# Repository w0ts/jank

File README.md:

# jank

**Ableton Link with no router.** jank protocol brings computers, MIDI gear and modular gear into a
**jank** session: the group mode of [Optimist](https://github.com/w0ts/optimist), the open firmware for the FM-1 synth
(**MODE JANK**, first called jam).

## No router

Link normally needs every player on the same network: a Wi-Fi router or access point that somebody sets up, joins and
keeps running. In jank there is none. The units send open Wi-Fi frames straight to each other on the group's channel,
with no association, no password and no host; the ones set to the same GROUP (1..9) hear each other and form one Link
session. Switch on, pick the group, play: on a stage, outdoors, wherever there is no network. How the frames look:
[docs/air.md](docs/air.md).

FM-1s running Optimist do this by themselves. **The jank device** speaks the same air format, so whatever is plugged
into it joins the group too.

## What joins through it

- **A computer, over the network.** On the device's USB port the computer sees a USB network adapter on the group, so
  any app with Ableton Link (Live, Bitwig…) joins the same session as the FM-1s.
- **A computer or a USB device, by MIDI clock.** The device is a USB-MIDI device for a computer, and a USB-MIDI host for
  gear with a USB port.
- **MIDI gear.** MIDI outputs send clock, start and stop locked to the session.
- **Modular gear.** Clock outputs, 5 V pulses.

It plays no sound: it follows the group's tempo and phase and sends them on. Link is Ableton's trademark; jank is not an
Ableton product.

## Two devices

- **The stick:** a bare Seeed XIAO ESP32-S3 (about US$7.50) in a computer or any USB host that speaks MIDI clock or Link (network driver). One button, one LED.
- **The jank box:** the same firmware on its own board, in a printed box.

The box has:
- 3 MIDI outs
- 1 MIDI in/out (TRS + DIN)
- 2 modular clock outs

## Build it

- [PCB](hardware/pcb/README.md)
- [Box](hardware/box/README.md)
- [Firmware](docs/firmware.md)

Details: [on the air](docs/air.md), [USB](docs/usb.md), [MIDI clock](docs/midi.md), [boards and pins](docs/boards.md).

## Licensing

The firmware (`firmware/`, `core/`, `tests/`, `scripts/`) is GPL-3.0-only, as it links Optimist's `link.c`
(`third_party/link`, copied from fm1-base, see its README). The control page and its test are MIT. The hardware
scripts carry GPL-3.0-only SPDX tags (`hardware/pcb/lib/stitch.py` CC0-1.0); the KiCad footprint of the XIAO is Seeed's,
CC BY-SA 4.0. See [LICENSE](LICENSE).

The pictures (`docs/img/`) are rendered from the box and board models by `docs/img/hero.scad`.

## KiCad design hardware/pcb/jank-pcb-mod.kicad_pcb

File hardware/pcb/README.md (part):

# jank board: schematic and layout for review

Part of the **[jank device](../../README.md)** · the other half: [the box](../box/README.md)

A carrier board for a **Seeed XIAO ESP32S3**: jank as one stick with a second USB-C for power, **a 0.91" OLED, an
encoder and two buttons (OK, BACK) on the lid side**, one RGB beat LED and **four MIDI outputs**. **v5 fits both
connectors on every output**: a right-angle 3.5 mm jack (XKB PJ-320D-B-SMT, surface mount) on the **top** and a DIN-5
(HOOYA DIN-504B-M10) on the **bottom**, **the jack beside the DIN** (v5c, 2026-11-09: between two DIN plates at a 23.0 mm
pitch, so nothing of the jack goes through the board under a DIN body) on the same nets (in parallel: **plug one at a
time**), and a **TRS type A / B slide switch** per output for the jack. **Both faces sit at the box wall** (the box
brings the board edge to 1.0 mm inside its outer face). **OUT1 doubles as a MIDI IN** under software control (an H11L1 behind a MOSFET
gate; its source cut by a second MOSFET). **Three outputs (OUT2, OUT3, OUT4) are on the front edge; OUT1 is on the back
edge** beside the two USB-Cs. **The top of the board is the lid side**: the XIAO, the screen, the encoder, the buttons,
the LED, the jacks and the A/B switches; the bottom carries only the DINs and the standing resistors (hand-soldered), and the
board stands about 20 mm above the box's floor on the DINs. Everything is hand-solderable: through-hole DINs,
switches, encoder, opto and swappable resistors, the jacks' four tabs, SOT-23 / SC-70 ICs, 0805 / 1206 passives, an LED
with lengthened pads. **The modular board (the one built): 87.0 x 79.5 mm, 2 layers.** (The plain 84 x 67 variant is
parked since v5c: with the 23 mm pitch its OUT4 resistor group lands on the encoder; `make_fab.sh` builds `-mod` only.)

> **Stage: schematic and layout, v5 (2026-11-08).** Nothing is ordered, built or measured. Every value marked
> *unverified* below was not checked against the part or a datasheet in this session.

The drawing: [`jank-pcb-mod-schematic.pdf`](jank-pcb-mod-schematic.pdf). The board: [`render-top-mod.png`](render-top-mod.png),
[`render-bottom-mod.png`](render-bottom-mod.png).

## v5c (2026-11-09): the jack beside the DIN, both faces at the wall

The user, on seeing v5's stacked connectors: *"the jacks are not reachable from the outside of the box ... put the midi
jack between the DIN plugs on the pcb, making sure the pins don't collide (DIN on one side, jack on the other)"*, and
*"DIN AND jack should be at the wall"*.

- **Each output's 3.5 mm jack moved 11.5 mm along the edge**, into the 2.1 mm gap between two DIN plates (the pitch
  went from 21.1 to **23.0 mm**; the board from 84 to **87 mm** wide so OUT4's resistor group clears the right
  channels' drivers, which moved 3 mm right with the wall jacks and the holes H1 / H2). OUT4's jack is right of the
  last DIN; **OUT1's jack is left of its DIN at the back-left corner** (DIN axis x 17.5, jack x 6.0).
- **The jack is now the surface-mount twin, XKB PJ-320D-B-SMT (C2884940)**: same body, bushing and pegs, four 1.5 x 2.5
  tabs on the top instead of legs through the board (the legs would have come out under the neighbouring DIN bodies).
  Its two 1.3 mm pegs sit in the gap, 0.4 mm from each DIN body. The side-wall jacks J11..J14 stay the through-hole
  PJ-320A (nothing is under them).
- **The DIN plate is 1.0 mm behind the board edge, the jack body front 0.5 mm past it.** The box puts the board edge
  1.0 mm inside its outer face on the connector edges: **the DIN faces are flush with the outside, the jack bodies 0.5 mm
  inside it with the bushings 1.5 mm proud**. The 1.0 mm also keeps the jack's rear tab pads 0.3 mm from the next DIN's
  pin 1 / 3 pads (the rows interleave: DIN pins at 13.3 and 15.8 in, jack tabs at 2.5 .. 11.0 in).
- **OUT1's A/B switch SW2 is the surface-mount XKB SS-3235S-L2 (C500056)**, over the DIN body at (17.5, 8.1): a
  through-hole switch's pins would hit the DIN under the board, and the strip east of the DIN carries the XIAO's MIDI IN
  lines (IN_EN, MIDI_RX, TX1). Same pinout (1-2-3 / 4-5-6, 2 and 5 the commons), knob 3.0 mm, travel 1.5 mm along x.
  SW3..SW5 stay the through-hole MSS22D18 (their pins land behind the DIN bodies).
- Routes: each jack's tip and ring reach their tabs through a via next to the pad (the switches' routes run on the
  bottom); OUT1's TIP throw crosses under the switch through two vias.
- Prices of the two new parts not read (LCSC refused the page on 2026-11-09): **0.00 in the BOM**, fill in before
  trusting the total.
- **The MIDI resistors are 1206s placed by JLC (later on 2026-11-09, the user: "the upright resistors are just post
  fixes"):** R3k 10 ohm (C17903), the source two 68 ohm in parallel, R4k + R8k (C17976; 34 ohm, 0.5 W together, for a
  mono plug on a TRS output: 0.33 W), R9 330 ohm for the LED (C17930). R8k sits where the 33 ohm group's bypass jumper
  JP2k was (gone). The axial pads (R1k, R2k, R8) stay, empty ("DNP fix"): a bench fix solders an axial part there with
  the 1206s removed. The 10 ohm group keeps its bypass jumper JP1k.
- **The screen is the 0.96" 128 x 64 OLED** (HS96L03W2C03, C5248080; the user, 2026-11-09): 27.3 x 27.8 on its header
  at (34.58, 24.0); the PCF8574 moved right of it; SDA / SCL swapped on the XIAO (SDA D8 = GPIO7, SCL D9 = GPIO8); the
  expander's right channels on P2 / P3, P4..P7 on test pads.

## v5 in short (what changed from round 7 / 2026-11-08)

- **Both connectors fitted, two rows on the front wall:** the jacks above the board, the DIN faces below it (OUT1 the
  same on the back wall). The DIN's footprint is mirrored onto the bottom; its plate sits **1.0 mm behind the edge**
  (the jacks' fronts stay on the edge) so its pin 2 clears the jack's back (below, "Both connectors").
- **The lid side is the top:** the XIAO, the OLED, OK, BACK, the encoder, one LED, the jacks, the A/B switches. Seen
  from the front with the lid up the outputs read **2, 3, 4 left to right** (OUT2 is now at x 10.45).
- **Pins:** OUT2, OUT3 and OUT4 share **one TX pad** (GPIO2); OUT1 keeps its own (GPIO1, Hi-Z in IN mode). That frees
  GPIO7 / GPIO8 for **I2C** (the OLED); IN_EN and MIDI_RX moved to GPIO5 / GPIO6, the LED to GPIO4.
- **The buttons are OK (menu / select) and BACK** (were MODE and PLAY/STOP): the same parts and ladder values.
- **One LED**, top-emitting (SK6812MINI-HS); the second LED and the reverse-mount cut-outs are gone.
- **4 M2 holes** (two right corners, two on the left edge between OUT1 and OUT2).
- **The standing resistors hang under the board** (beside the DINs); their jumpers and parallel pads stay on top.
- **BOM:** one board, 4 jacks + 4 DINs + 4 A/B switches, the OLED, one LED: **USD 17.49** at unit prices, **USD 30.84**
  with each shop's minimum order (`BOM.md`).

## Files

| File | What |
|---|---|
| `make_schematic.py` | The schematic, the project (with the board's rules), the XIAO and switch symbols, the intended nets and `BOM.md`, from one parts table |
| `make_footprints.py` | The v5 output footprint `MIDI_OUT_PJ-320A_top_DIN-504B-M10_bottom`, the LED `LED_SK6812MINI-HS_3.7x3.5mm_HandSolder`, the OLED header `OLED_0.91in_128x32_I2C_HS91L02W2C01`, the A/B slide switch, the XIAO on headers, and the older output footprints (`lib/jank.pretty/`) |
| `make_board.py` | `jank-pcb.kicad_pcb`: placement, routes, pours, stitching vias, silk (KiCad's Python). Its `square` layout (an older 67 x 58 board) is unused and not built |
| `make_mockup.py` | `mockup.stl` (its `mockup.scad` is rebuilt, not kept): the board and its parts as one solid, both sides, checked by `../check_stl.py` |
| `make_assembly.py` | `fab/bom.csv` and `fab/cpl.csv`: JLCPCB's assembly files (README "Assembly") |
| `check_nets.py` | The netlist against the intent and the design rules (the A/B switches, the shared TX pad, the MIDI IN, the controls, the OLED), and the board's pads against the schematic |
| `make_fab.sh` | All of it in order, for both projects (v5 and the modular variant, `MODULAR=1`): schematic, ERC, PDF, the board, DRC, nets, Gerbers + drill, the assembly files, renders, mockup |
| `jank-pcb.kicad_sch`, `jank-pcb.kicad_pcb`, `jank-pcb.kicad_pro`, `sym-lib-table`, `fp-lib-table` | The KiCad 10 project (generated) |
| `lib/jank.kicad_sym` | The XIAO ESP32S3 and DPDT slide switch symbols (drawn by `make_schematic.py`) |
| `lib/jank.pretty/XIAO-ESP32-S3-DIP.kicad_mod` | Seeed's footprint, unchanged (source below) |
| `lib/jank.pretty/XIAO-ESP32-S3-DIP_Headers.kicad_mod` | The same with its courtyard on the two pin rows only (written by `make_footprints.py`): on headers, low parts fit under the module |
| `lib/stitch.py` | The ground stitching vias, from optimist's SD board (after m-card, CC0-1.0) |
| `jank-pcb-schematic.pdf`, `render-top.png`, `render-bottom.png` | The schematic (A2) and the board's renders |
| `fab/jank-pcb-gerbers.zip` | **For JLCPCB** (bare board): the Gerbers and the PTH / NPTH drill files, origin at the lower left (the `fab/gerbers/` folder and the reports are rebuilt by `make_fab.sh`, not kept) |
| `fab/bom.csv`, `fab/cpl.csv` | **For JLCPCB's assembly**: the SMD parts it places and where (generated by `make_assembly.py`); `fab/full/` the same with the through-hole parts, for later |
| `BOM.md` | Parts, one price each, shop and date (generated) |
| `jank-pcb-mod.*`, `BOM-mod.md`, `fab/mod/`, `render-*-mod.png`, `mockup-mod.stl`, `jank-pcb-mod-schematic.pdf` | The modular variant (README "Modular variant") |

```
sh hardware/pcb/make_fab.sh        # needs KiCad 10 (kicad-cli and its Python), python3, OpenSCAD
```

**Last run (2026-11-08, v5):**
- ERC: **0 errors, 0 warnings**.
- DRC: **0 errors, 0 unconnected, 28 warnings**: 21 "silkscreen over copper" (Seeed's XIAO outline over its own pads,
  the A/B switches' outlines and their "OUTk A|B" labels over tracks, one LED outline line over its data track) and 7
  "silkscreen clipped by the board edge" (the XIAO's USB-C lip drawn past the back edge, where the socket really
  overhangs).
- `check_nets.py`: 243 schematic pins, 45 nets, 0 problems; **278 board pads against the schematic, 0 differences**.
- Mockup: `mockup.stl` one body, **0 open edges**, 0 non-manifold, 0 misoriented.

**XIAO footprint source:** `XIAO-ESP32-S3-DIP.kicad_mod` from Seeed's
[OPL_Kicad_Library](https://github.com/Seeed-Studio/OPL_Kicad_Library), folder "Seeed Studio XIAO Series Library",
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
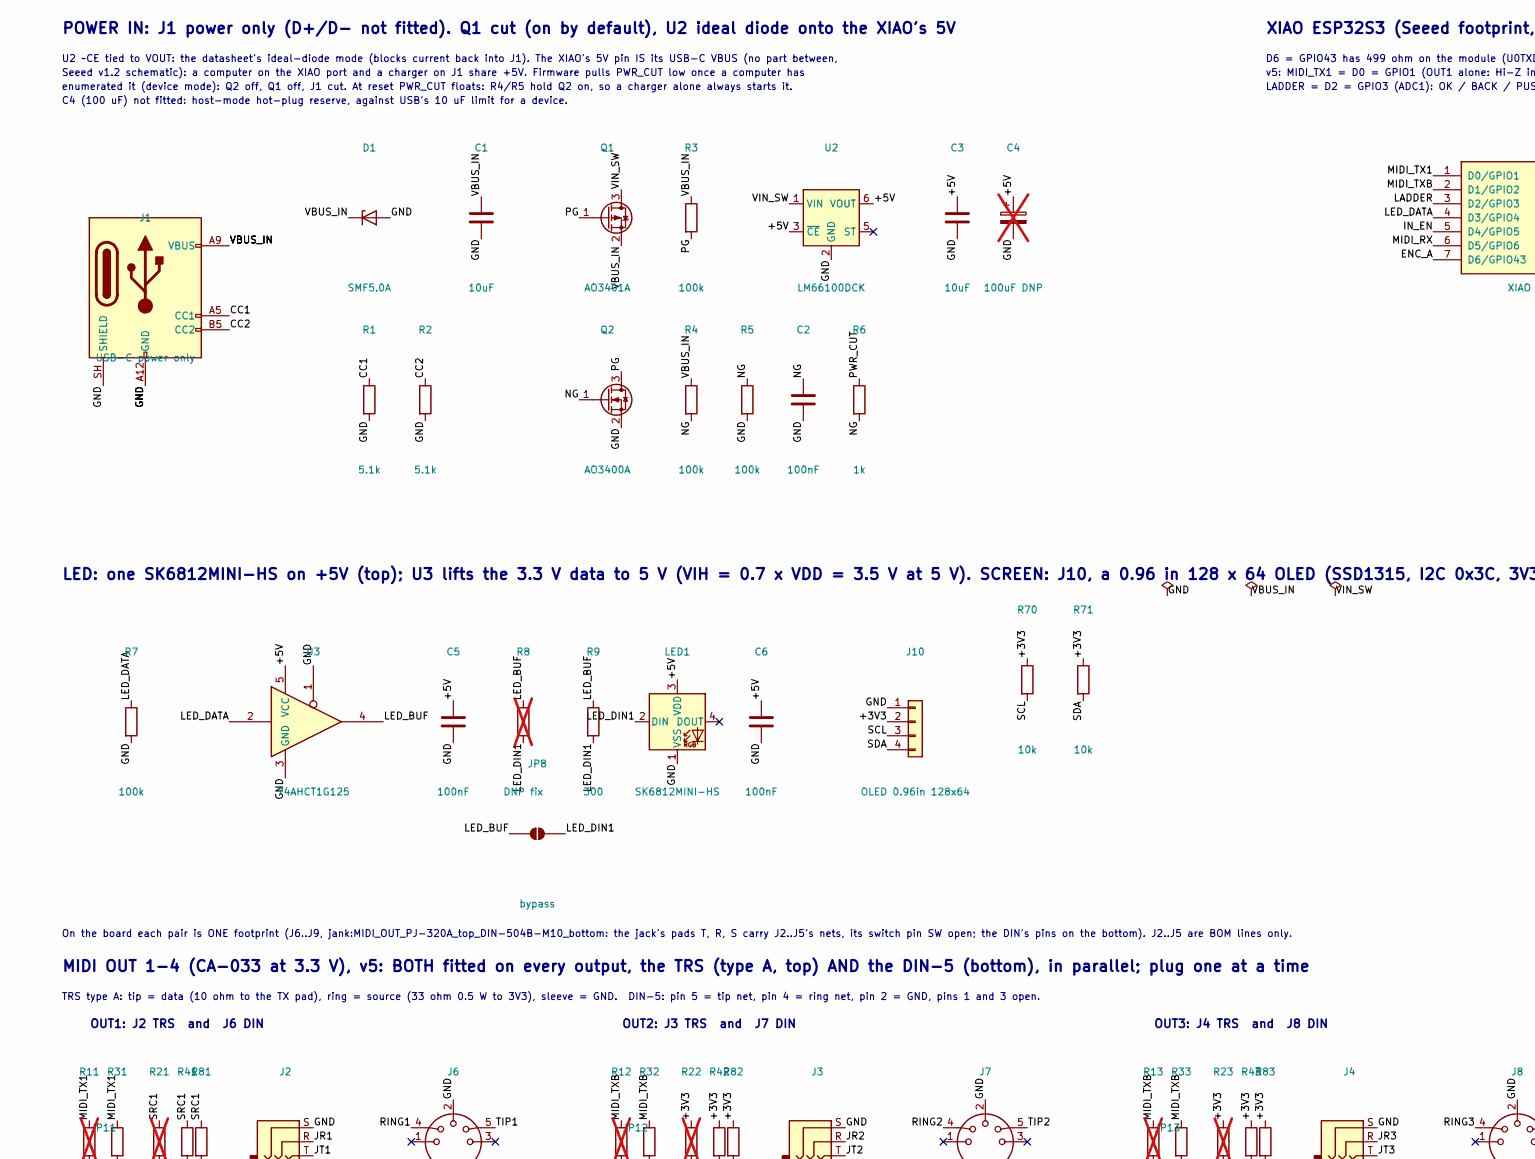
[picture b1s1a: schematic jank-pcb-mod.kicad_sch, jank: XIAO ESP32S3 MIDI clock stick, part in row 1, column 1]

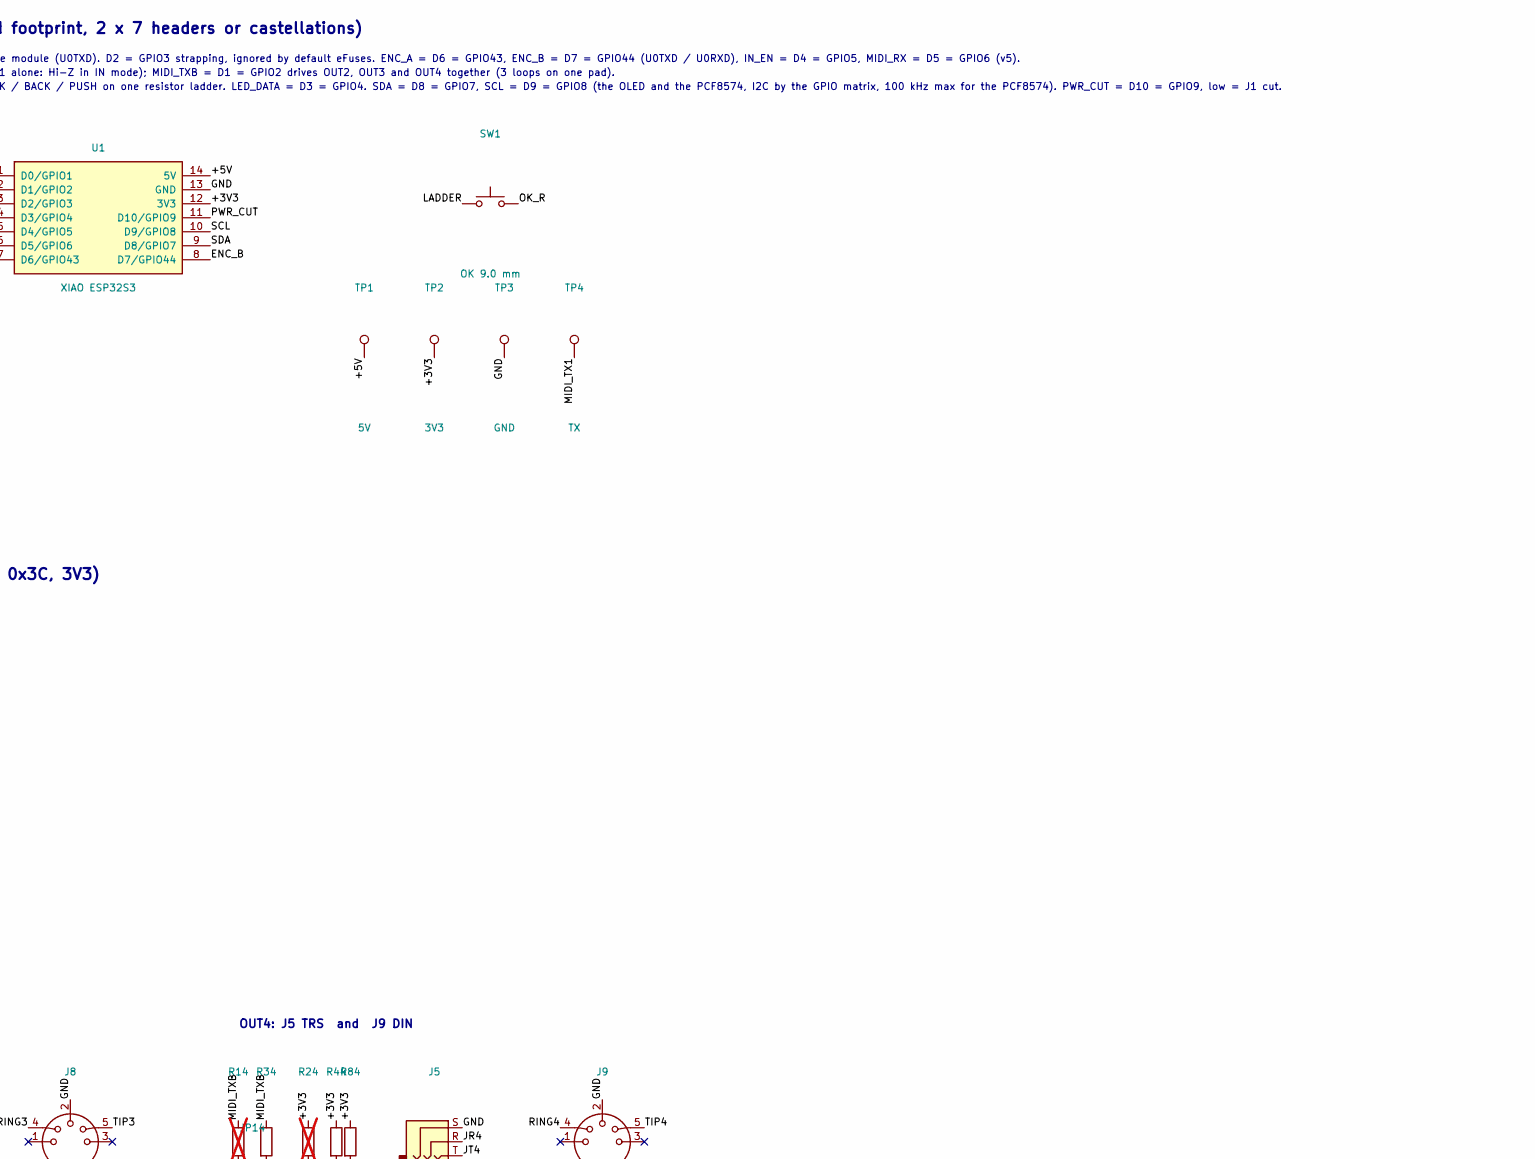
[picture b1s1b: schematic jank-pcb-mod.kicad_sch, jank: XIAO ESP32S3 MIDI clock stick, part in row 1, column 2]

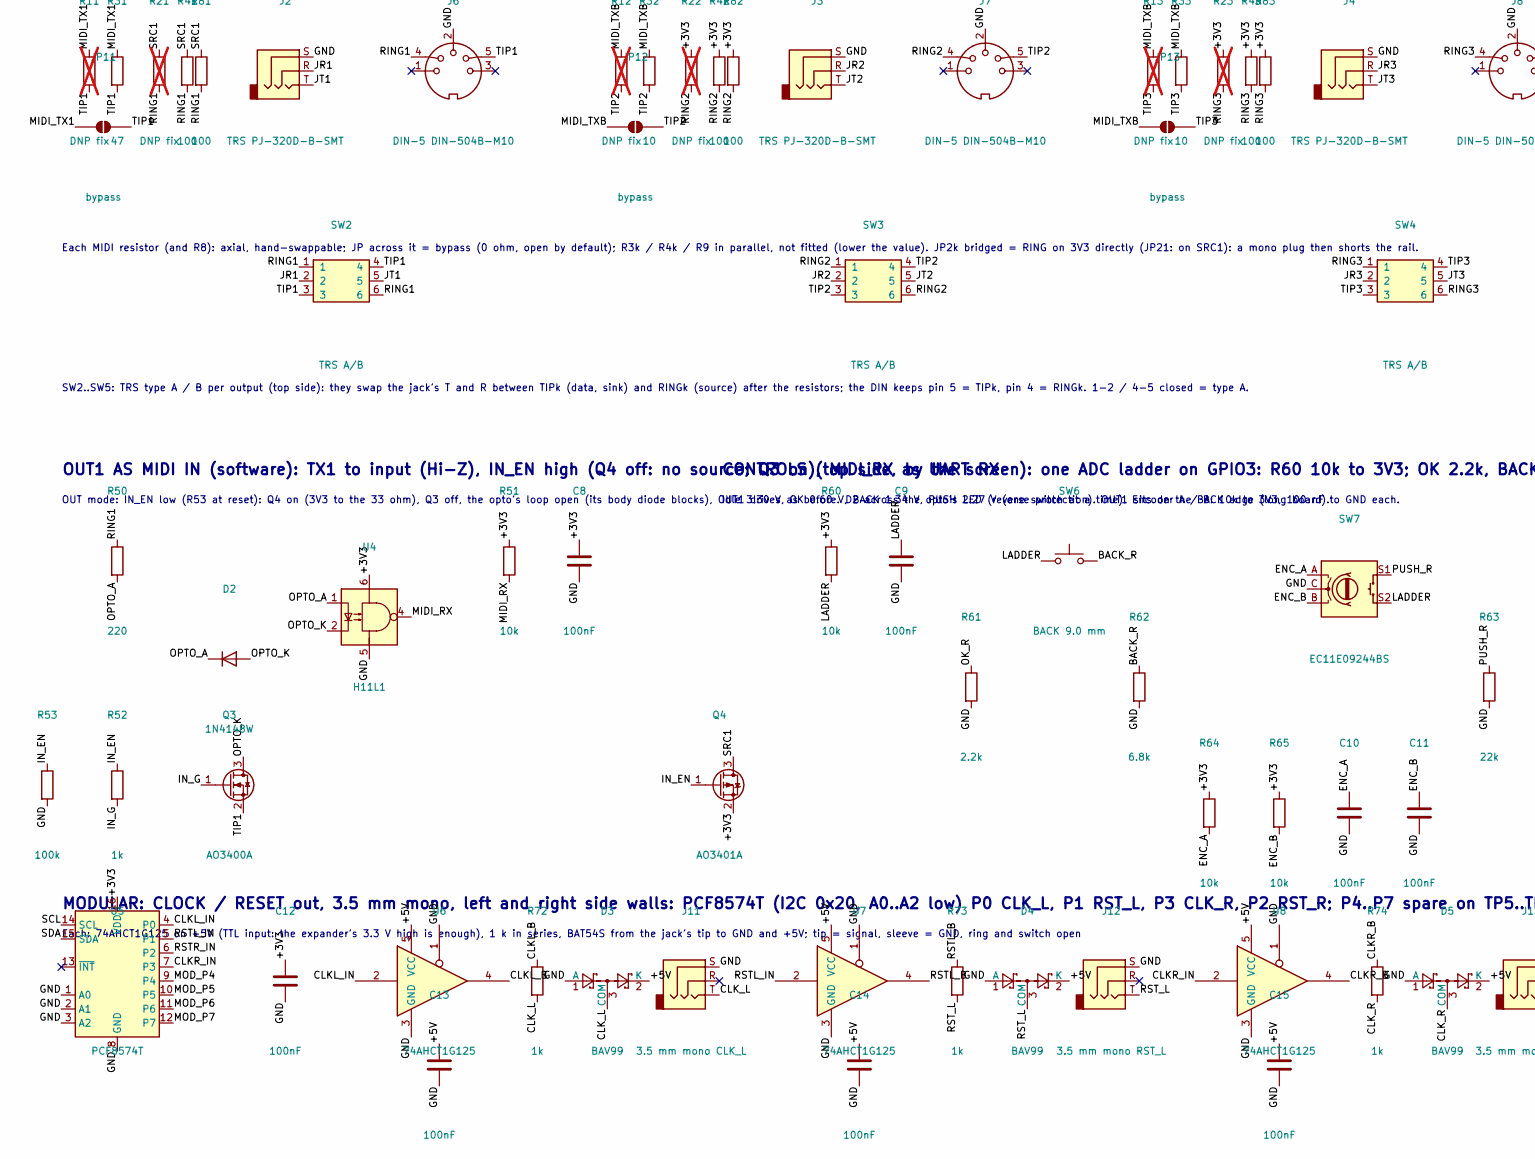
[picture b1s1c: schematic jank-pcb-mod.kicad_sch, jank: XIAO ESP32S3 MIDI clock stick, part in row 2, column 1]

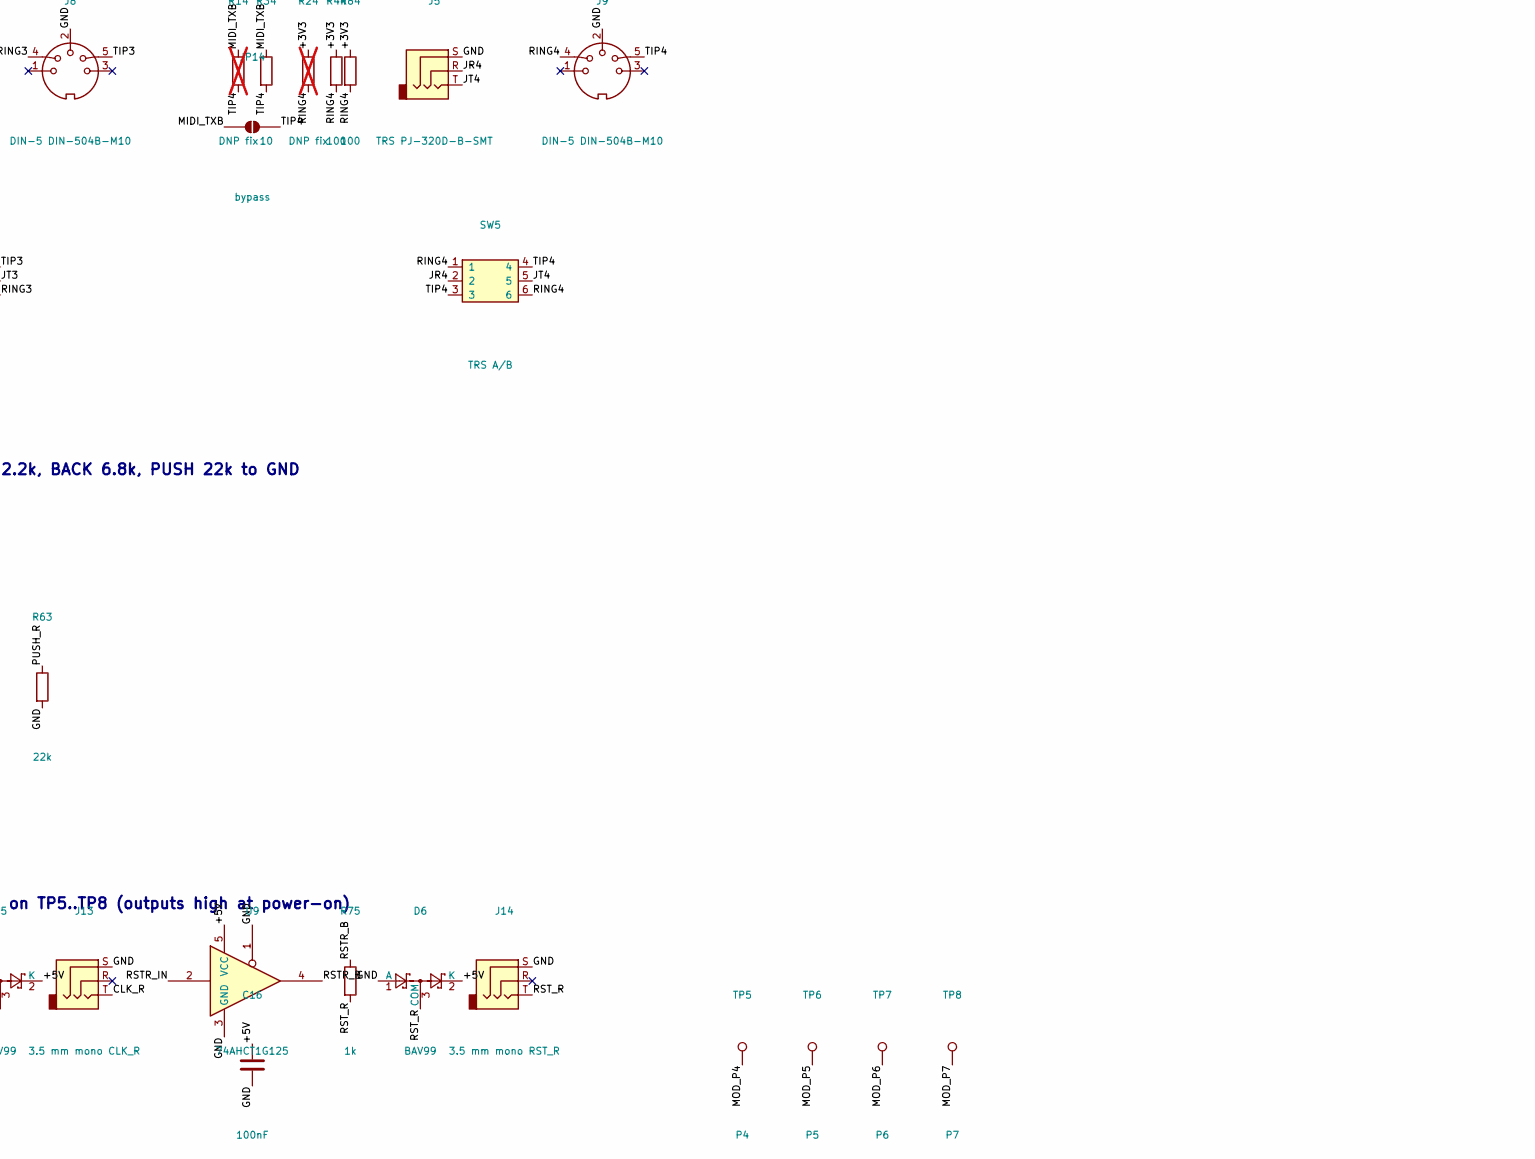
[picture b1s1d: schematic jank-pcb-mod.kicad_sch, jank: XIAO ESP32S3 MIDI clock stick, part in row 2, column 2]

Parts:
C1, C3: 10uF; C_0805_2012Metric_Pad1.18x1.45mm_HandSolder; MPN Samsung CL21A106KAYNNNE
C2, C5, C6, C8, C9, C10, C11, C12, C13, C14, C15, C16: 100nF; C_0805_2012Metric_Pad1.18x1.45mm_HandSolder; MPN YAGEO CC0805KRX7R9BB104
C4: 100uF DNP; CP_Elec_5x5.4; MPN ROQANG RVT1C101M0505; not fitted
D1: SMF5.0A; D_SOD-123F; MPN MDD SMF5.0A
D2: 1N4148W; D_SOD-123; MPN Semtech 1N4148W
D3, D4, D5, D6: BAV99; SOT-23; MPN BAV99
J1: USB-C power only; USB_C_SHOUHAN_TYPE-C-6P; MPN SHOU HAN TYPE-C 6P
J2, J3, J4, J5: TRS PJ-320D-B-SMT; MPN XKB PJ-320D-B-SMT
J6, J7, J8, J9: DIN-5 DIN-504B-M10; MIDI_OUT_PJ-320A_top_DIN-504B-M10_bottom; MPN HOOYA DIN-504B-M10
J10: OLED 0.96in 128x64; OLED_0.96in_128x64_I2C_HS96L03W2C03; MPN HS HS96L03W2C03
J11: 3.5 mm mono CLK_L; Jack_3.5mm_XKB_PJ-320A_Horizontal; MPN XKB PJ-320A
J12: 3.5 mm mono RST_L; Jack_3.5mm_XKB_PJ-320A_Horizontal; MPN XKB PJ-320A
J13: 3.5 mm mono CLK_R; Jack_3.5mm_XKB_PJ-320A_Horizontal; MPN XKB PJ-320A
J14: 3.5 mm mono RST_R; Jack_3.5mm_XKB_PJ-320A_Horizontal; MPN XKB PJ-320A
JP8, JP11, JP12, JP13, JP14: bypass; SolderJumper-2_P1.3mm_Open_RoundedPad1.0x1.5mm
LED1: SK6812MINI-HS; LED_SK6812MINI-HS_3.7x3.5mm_HandSolder; MPN OPSCO SK6812MINI-HS
Q1, Q4: AO3401A; SOT-23; MPN AOS AO3401A
Q2, Q3: AO3400A; SOT-23; MPN AOS AO3400A
R1, R2: 5.1k; R_0805_2012Metric_Pad1.20x1.40mm_HandSolder; MPN UNI-ROYAL 0805W8F5101T5E
R3, R4, R5, R7, R53: 100k; R_0805_2012Metric_Pad1.20x1.40mm_HandSolder; MPN UNI-ROYAL 0805W8F1003T5E
R6, R52, R72, R73, R74, R75: 1k; R_0805_2012Metric_Pad1.20x1.40mm_HandSolder; MPN UNI-ROYAL 0805W8F1001T5E
R8, R11, R12, R13, R14: DNP fix; R_Axial_DIN0207_L6.3mm_D2.5mm_P2.54mm_Vertical; not fitted
R9: 300; R_1206_3216Metric_Pad1.30x1.75mm_HandSolder; MPN UNI-ROYAL 1206W4F3000T5E
R21, R22, R23, R24: DNP fix; R_Axial_DIN0309_L9.0mm_D3.2mm_P2.54mm_Vertical; not fitted
R31: 47; R_1206_3216Metric_Pad1.30x1.75mm_HandSolder; MPN UNI-ROYAL 1206W4F470JT5E
R32, R33, R34: 10; R_1206_3216Metric_Pad1.30x1.75mm_HandSolder; MPN UNI-ROYAL 1206W4F100JT5E
R41, R42, R43, R44, R81, R82, R83, R84: 100; R_1206_3216Metric_Pad1.30x1.75mm_HandSolder; MPN UNI-ROYAL 1206W4F1000T5E
R50: 220; R_0805_2012Metric_Pad1.20x1.40mm_HandSolder; MPN UNI-ROYAL 0805W8F2200T5E
R51, R60, R64, R65, R70, R71: 10k; R_0805_2012Metric_Pad1.20x1.40mm_HandSolder; MPN UNI-ROYAL 0805W8F1002T5E
R61: 2.2k; R_0805_2012Metric_Pad1.20x1.40mm_HandSolder; MPN UNI-ROYAL 0805W8F2201T5E
R62: 6.8k; R_0805_2012Metric_Pad1.20x1.40mm_HandSolder; MPN UNI-ROYAL 0805W8F6801T5E
R63: 22k; R_0805_2012Metric_Pad1.20x1.40mm_HandSolder; MPN UNI-ROYAL 0805W8F2202T5E
SW1: OK 9.0 mm; SW_PUSH_6mm; MPN HRO K2-1102DP-K4SW-04
SW2: TRS A/B; SW_Slide_DPDT_SS3235S_SMD; MPN XKB SS-3235S-L2
SW3, SW4, SW5: TRS A/B; SW_Slide_DPDT_MSS22D18; MPN SHOU HAN MSS22D18G2
SW6: BACK 9.0 mm; SW_PUSH_6mm; MPN HRO K2-1102DP-K4SW-04
SW7: EC11E09244BS; RotaryEncoder_Alps_EC11E-Switch_Vertical_H20mm; MPN ALPS EC11E09244BS
TP1: 5V; TestPoint_Pad_D1.5mm
TP2: 3V3; TestPoint_Pad_D1.5mm
TP3: GND; TestPoint_Pad_D1.5mm
TP4: TX; TestPoint_Pad_D1.5mm
TP5: P4; TestPoint_Pad_D1.0mm
TP6: P5; TestPoint_Pad_D1.0mm
TP7: P6; TestPoint_Pad_D1.0mm
TP8: P7; TestPoint_Pad_D1.0mm
U1: XIAO ESP32S3; XIAO-ESP32-S3-DIP; MPN 113991114
U2: LM66100DCK; SOT-363_SC-70-6; MPN TI LM66100DCKR
U3, U6, U7, U8, U9: 74AHCT1G125; SOT-23-5_HandSoldering; MPN TI SN74AHCT1G125DBVR
U4: H11L1; DIP-6_W7.62mm; MPN EVERLIGHT H11L1
U5: PCF8574T; SOIC-16W_7.5x10.3mm_P1.27mm; MPN NXP PCF8574T/3

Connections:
+3V3: C8.1, C12.1, J10.2, Q4.2 (S), R22.1, R23.1, R24.1, R42.1, R43.1, R44.1, R51.1, R60.1, R64.1, R65.1, R70.1, R71.1, R82.1, R83.1, R84.1, TP2.1, U1.12 (3V3), U4.6, U5.16 (VDD)
+5V: C3.1, C4.1, C5.1, C6.1, C13.1, C14.1, C15.1, C16.1, D3.2 (K), D4.2 (K), D5.2 (K), D6.2 (K), LED1.3 (VDD), TP1.1, U1.14 (5V), U2.3 (~CE), U2.6 (VOUT), U3.5 (VCC), U6.5 (VCC), U7.5 (VCC), U8.5 (VCC), U9.5 (VCC)
BACK_R: R62.1, SW6.2
CC1: J1.A5 (CC1), R1.1
CC2: J1.B5 (CC2), R2.1
CLKL_B: R72.1, U6.4
CLKL_IN: U5.4 (P0), U6.2
CLKR_B: R74.1, U8.4
CLKR_IN: U5.7 (P3), U8.2
CLK_L: D3.3 (COM), J11.T, R72.2
CLK_R: D5.3 (COM), J13.T, R74.2
ENC_A: C10.1, R64.2, SW7.A, U1.7 (D6/GPIO43)
ENC_B: C11.1, R65.2, SW7.B, U1.8 (D7/GPIO44)
GND: C1.2, C2.2, C3.2, C4.2, C5.2, C6.2, C8.2, C9.2, C10.2, C11.2, C12.2, C13.2, C14.2, C15.2, C16.2, D1.2 (A), D3.1 (A), D4.1 (A), D5.1 (A), D6.1 (A), J1.A12 (GND), J1.B12 (GND), J1.SH (SHIELD), J2.S, J3.S, J4.S, J5.S, J6.2, J6.E, J6.S, J7.2, J7.E, J7.S, J8.2, J8.E, J8.S, J9.2, J9.E, J9.S, J10.1, J11.S, J12.S, J13.S, J14.S, LED1.1 (VSS), Q2.2 (S), R1.2, R2.2, R5.2, R7.2, R53.2, R61.2, R62.2, R63.2, SW7.C, TP3.1, U1.13 (GND), U2.2 (GND), U3.1, U3.3 (GND), U4.5, U5.1 (A0), U5.2 (A1), U5.3 (A2), U5.8 (GND), U6.1, U6.3 (GND), U7.1, U7.3 (GND), U8.1, U8.3 (GND), U9.1, U9.3 (GND)
IN_EN: Q4.1 (G), R52.1, R53.1, U1.5 (D4/GPIO5)
IN_G: Q3.1 (G), R52.2
JR1: J2.R, J6.R, SW2.2
JR2: J3.R, J7.R, SW3.2
JR3: J4.R, J8.R, SW4.2
JR4: J5.R, J9.R, SW5.2
JT1: J2.T, J6.T, SW2.5
JT2: J3.T, J7.T, SW3.5
JT3: J4.T, J8.T, SW4.5
JT4: J5.T, J9.T, SW5.5
LADDER: C9.1, R60.2, SW1.1, SW6.1, SW7.S2, U1.3 (D2/GPIO3)
LED_BUF: JP8.1 (A), R8.1, R9.1, U3.4
LED_DATA: R7.1, U1.4 (D3/GPIO4), U3.2
LED_DIN1: JP8.2 (B), LED1.2 (DIN), R8.2, R9.2
MIDI_RX: R51.2, U1.6 (D5/GPIO6), U4.4
MIDI_TX1: JP11.1 (A), R11.1, R31.1, TP4.1, U1.1 (D0/GPIO1)
MIDI_TXB: JP12.1 (A), JP13.1 (A), JP14.1 (A), R12.1, R13.1, R14.1, R32.1, R33.1, R34.1, U1.2 (D1/GPIO2)
MOD_P4: TP5.1, U5.9 (P4)
MOD_P5: TP6.1, U5.10 (P5)
MOD_P6: TP7.1, U5.11 (P6)
MOD_P7: TP8.1, U5.12 (P7)
NG: C2.1, Q2.1 (G), R4.2, R5.1, R6.2
OK_R: R61.1, SW1.2
OPTO_A: D2.1 (K), R50.2, U4.1
OPTO_K: D2.2 (A), Q3.3 (D), U4.2
PG: Q1.1 (G), Q2.3 (D), R3.2
PUSH_R: R63.1, SW7.S1
PWR_CUT: R6.1, U1.11 (D10/GPIO9)
RING1: J6.4, R21.2, R41.2, R50.1, R81.2, SW2.1, SW2.6
RING2: J7.4, R22.2, R42.2, R82.2, SW3.1, SW3.6
RING3: J8.4, R23.2, R43.2, R83.2, SW4.1, SW4.6
RING4: J9.4, R24.2, R44.2, R84.2, SW5.1, SW5.6
RSTL_B: R73.1, U7.4
RSTL_IN: U5.5 (P1), U7.2
RSTR_B: R75.1, U9.4
RSTR_IN: U5.6 (P2), U9.2
RST_L: D4.3 (COM), J12.T, R73.2
RST_R: D6.3 (COM), J14.T, R75.2
SCL: J10.3, R70.2, U1.10 (D9/GPIO8), U5.14 (SCL)
SDA: J10.4, R71.2, U1.9 (D8/GPIO7), U5.15 (SDA)
SRC1: Q4.3 (D), R21.1, R41.1, R81.1
TIP1: J6.5, JP11.2 (B), Q3.2 (S), R11.2, R31.2, SW2.3, SW2.4
TIP2: J7.5, JP12.2 (B), R12.2, R32.2, SW3.3, SW3.4
TIP3: J8.5, JP13.2 (B), R13.2, R33.2, SW4.3, SW4.4
TIP4: J9.5, JP14.2 (B), R14.2, R34.2, SW5.3, SW5.4
VBUS_IN: C1.1, D1.1 (K), J1.A9 (VBUS), J1.B9 (VBUS), Q1.2 (S), R3.1, R4.1
VIN_SW: Q1.3 (D), U2.1 (VIN)

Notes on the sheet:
POWER IN: J1 power only (D+/D- not fitted). Q1 cut (on by default), U2 ideal diode onto the XIAO's 5V
U2 ~CE tied to VOUT: the datasheet's ideal-diode mode (blocks current back into J1). The XIAO's 5V pin IS its USB-C VBUS (no part between,
Seeed v1.2 schematic): a computer on the XIAO port and a charger on J1 share +5V. Firmware pulls PWR_CUT low once a computer has
enumerated it (device mode): Q2 off, Q1 off, J1 cut. At reset PWR_CUT floats: R4/R5 hold Q2 on, so a charger alone always starts it.
C4 (100 uF) not fitted: host-mode hot-plug reserve, against USB's 10 uF limit for a device.
XIAO ESP32S3 (Seeed footprint, 2 x 7 headers or castellations)
D6 = GPIO43 has 499 ohm on the module (U0TXD). D2 = GPIO3 strapping, ignored by default eFuses. ENC_A = D6 = GPIO43, ENC_B = D7 = GPIO44 (U0TXD / U0RXD), IN_EN = D4 = GPIO5, MIDI_RX = D5 = GPIO6 (v5).
v5: MIDI_TX1 = D0 = GPIO1 (OUT1 alone: Hi-Z in IN mode); MIDI_TXB = D1 = GPIO2 drives OUT2, OUT3 and OUT4 together (3 loops on one pad).
LADDER = D2 = GPIO3 (ADC1): OK / BACK / PUSH on one resistor ladder. LED_DATA = D3 = GPIO4. SDA = D8 = GPIO7, SCL = D9 = GPIO8 (the OLED and the PCF8574, I2C by the GPIO matrix, 100 kHz max for the PCF8574). PWR_CUT = D10 = GPIO9, low = J1 cut.
LED: one SK6812MINI-HS on +5V (top); U3 lifts the 3.3 V data to 5 V (VIH = 0.7 x VDD = 3.5 V at 5 V). SCREEN: J10, a 0.96 in 128 x 64 OLED (SSD1315, I2C 0x3C, 3V3)
MIDI OUT 1-4 (CA-033 at 3.3 V), v5: BOTH fitted on every output, the TRS (type A, top) AND the DIN-5 (bottom), in parallel; plug one at a time
TRS type A: tip = data (10 ohm to the TX pad), ring = source (33 ohm 0.5 W to 3V3), sleeve = GND. DIN-5: pin 5 = tip net, pin 4 = ring net, pin 2 = GND, pins 1 and 3 open.
OUT1: J2 TRS and J6 DIN
OUT2: J3 TRS and J7 DIN
OUT3: J4 TRS and J8 DIN
OUT4: J5 TRS and J9 DIN
SW2..SW5: TRS type A / B per output (top side): they swap the jack's T and R between TIPk (data, sink) and RINGk (source) after the resistors; the DIN keeps pin 5 = TIPk, pin 4 = RINGk. 1-2 / 4-5 closed = type A.
OUT1 AS MIDI IN (software): TX1 to input (Hi-Z), IN_EN high (Q4 off: no source; Q3 on), MIDI_RX as UART RX
OUT mode: IN_EN low (R53 at reset): Q4 on (3V3 to the 33 ohm), Q3 off, the opto's loop open (its body diode blocks), OUT1 drives as before. D2 across the opto's LED (reverse protection). OUT1 sits on the BACK edge (long board).
CONTROLS (top side, by the screen): one ADC ladder on GPIO3: R60 10k to 3V3; OK 2.2k, BACK 6.8k, PUSH 22k to GND
Idle 3.30 V, OK 0.60 V, BACK 1.34 V, PUSH 2.27 V (one switch at a time). Encoder A / B: 10k to 3V3, 100 nF to GND each.
Each MIDI resistor (and R8): axial, hand-swappable; JP across it = bypass (0 ohm, open by default); R3k / R4k / R9 in parallel, not fitted (lower the value). JP2k bridged = RING on 3V3 directly (JP21: on SRC1): a mono plug then shorts the rail.
On the board each pair is ONE footprint (J6..J9, jank:MIDI_OUT_PJ-320A_top_DIN-504B-M10_bottom: the jack's pads T, R, S carry J2..J5's nets, its switch pin SW open; the DIN's pins on the bottom). J2..J5 are BOM lines only.
MODULAR: CLOCK / RESET out, 3.5 mm mono, left and right side walls: PCF8574T (I2C 0x20, A0..A2 low) P0 CLK_L, P1 RST_L, P3 CLK_R, P2 RST_R; P4..P7 spare on TP5..TP8 (outputs high at power-on)
Each: 74AHCT1G125 on +5V (TTL input: the expander's 3.3 V high is enough), 1 k in series, BAT54S from the jack's tip to GND and +5V; tip = signal, sleeve = GND, ring and switch open

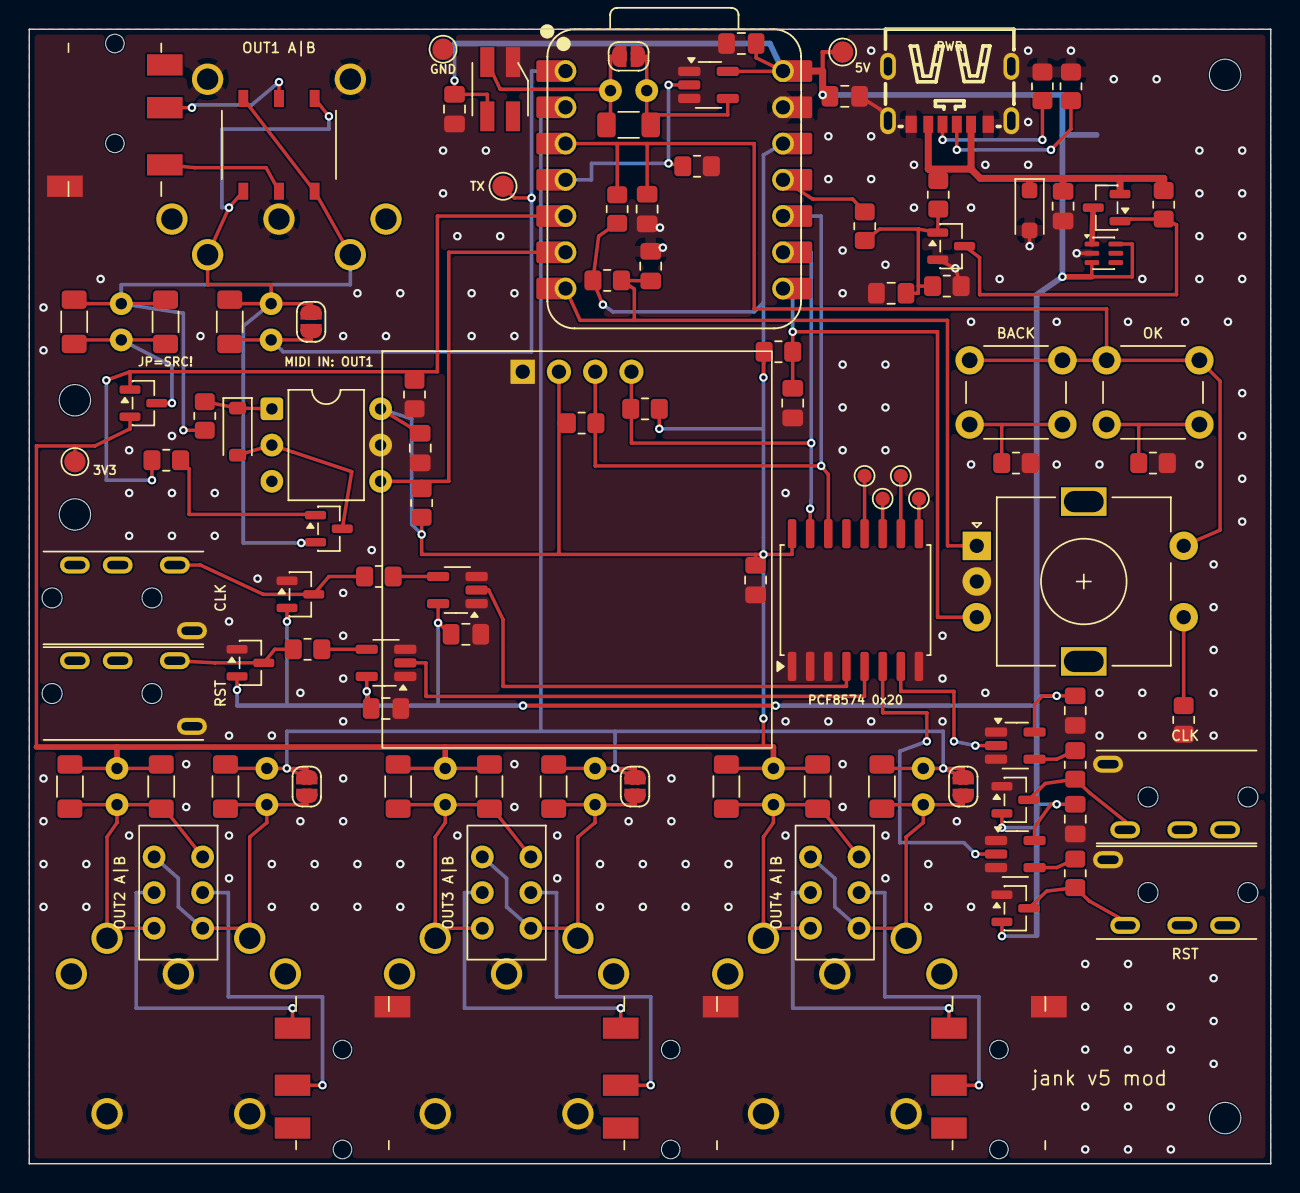
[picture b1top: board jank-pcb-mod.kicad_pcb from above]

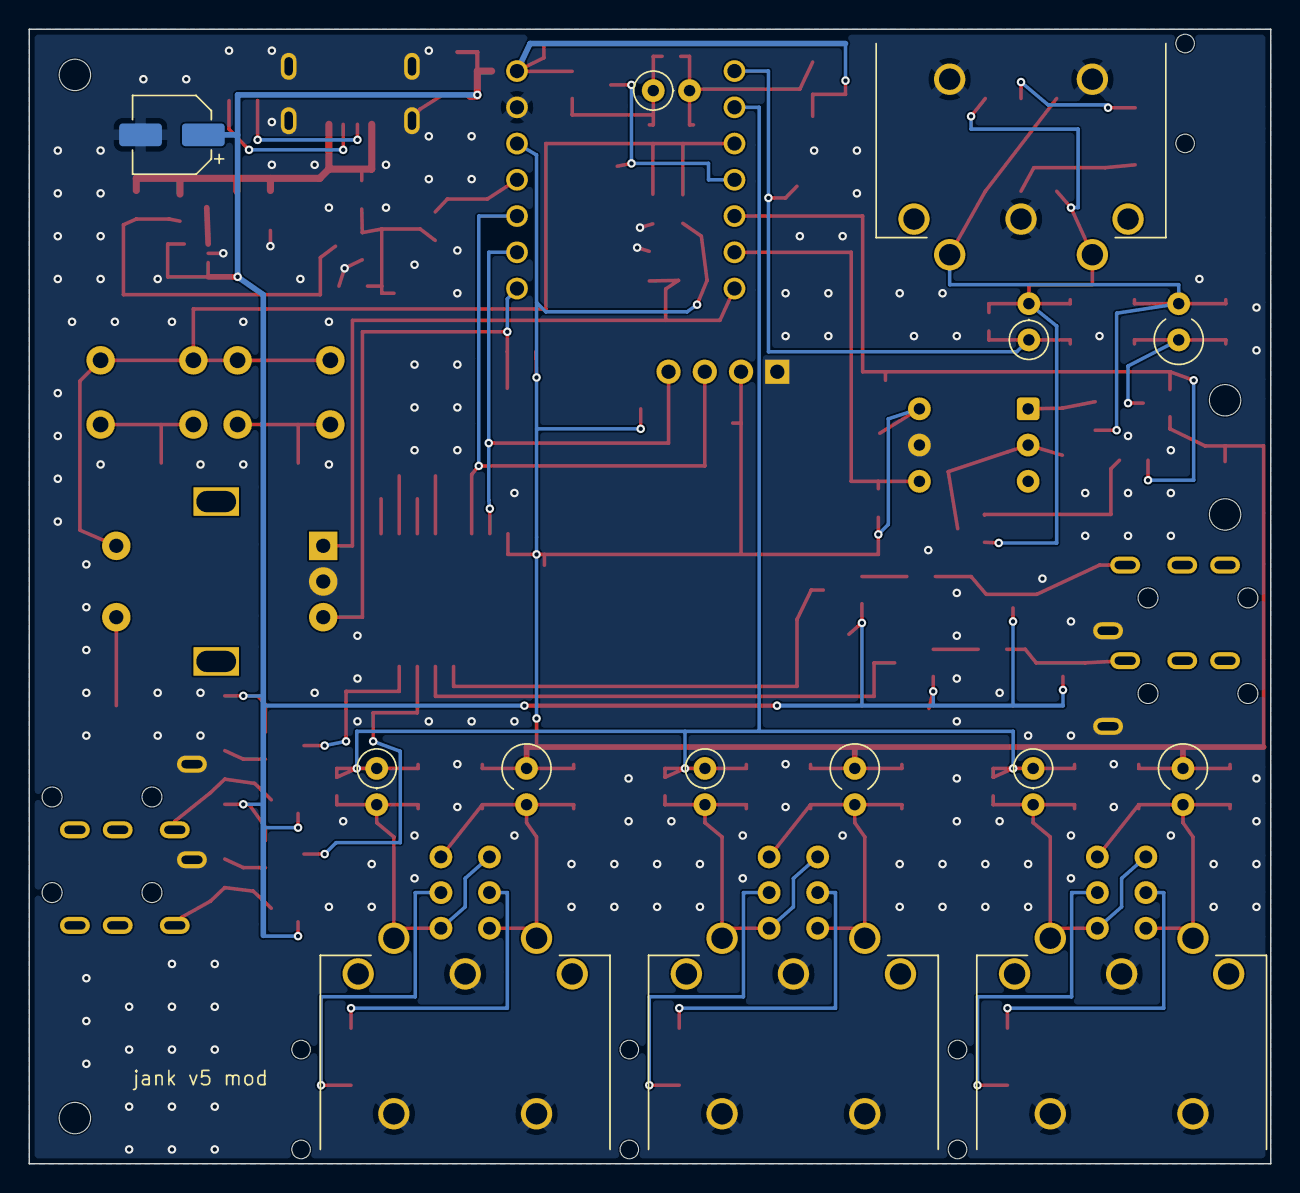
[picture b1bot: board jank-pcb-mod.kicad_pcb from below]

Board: 2 copper layers, 87.0 x 79.5 mm, 114 parts (10 on the bottom side), 61 nets.

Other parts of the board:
H1, H2, H3, H4: M2; MountingHole_2.2mm_M2

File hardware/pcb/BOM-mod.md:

# jank board (modular variant): bill of materials

Generated by `make_schematic.py`. One price each, read on 2026-11-08 from the shop named, at its first price break, before VAT and shipping. LCSC prices come from LCSC's own product data (USD). Nothing here was ordered.

v5: every output has BOTH connectors fitted, the 3.5 mm jack on the top and the DIN-5 on the bottom (in parallel,
plug one at a time), and its TRS A/B switch. One board: 4 jacks, 4 DINs, 4 A/B switches, the OLED, one LED. **Modular variant** (`jank-pcb-mod`): plus 4 mono jacks (CLOCK / RESET, both side walls), the PCF8574T, 4 buffers, 4 x 1 k, 4 BAT54S, 5 x 100 nF.

| Refs | Qty | Part | MPN | Shop, code | Unit | Min order |
|---|---|---|---|---|---|---|
| U1 | 1 | Seeed XIAO ESP32S3 (plain, not Sense), no headers included | 113991114 | Seeed Studio seeedstudio.com XIAO-ESP32S3-p-5627 | USD 7.4900 | 1 |
| (U1) | 2 | Pin header 1x7, 2.54 mm (the XIAO's legs: parts sit under the module) | PZ254V-11-07P | LCSC C492406 | USD 0.0467 | 10 |
| J1 | 1 | USB-C receptacle, power only, 6 pins + 4 through-hole shell legs (v5c 2026-11-09: in JLC stock; the GCT USB4125 had none) | SHOU HAN TYPE-C 6P | LCSC C456012 | USD 0.0390 | 1 |
| R1, R2 | 2 | Resistor 5.1k 1% 0805 | UNI-ROYAL 0805W8F5101T5E | LCSC C27834 | USD 0.0055 | 100 |
| D1 | 1 | TVS 5.0 V unidirectional, SOD-123F | MDD SMF5.0A | LCSC C193402 | USD 0.0285 | 20 |
| C1, C3 | 2 | Capacitor 10uF 25V X5R 0805 | Samsung CL21A106KAYNNNE | LCSC C15850 | USD 0.0362 | 20 |
| Q1, Q4 | 2 | P-MOSFET 30 V 4 A, SOT-23 | AOS AO3401A | LCSC C15127 | USD 0.0835 | 5 |
| Q2, Q3 | 2 | N-MOSFET 30 V, Vgs(th) max 1.45 V (listing), SOT-23 | AOS AO3400A | LCSC C20917 | USD 0.0899 | 5 |
| R3, R4, R5, R7, R53 | 5 | Resistor 100k 1% 0805 | UNI-ROYAL 0805W8F1003T5E | LCSC C149504 | USD 0.0060 | 100 |
| R6, R52, R72, R73, R74, R75 | 6 | Resistor 1k 1% 0805 | UNI-ROYAL 0805W8F1001T5E | LCSC C17513 | USD 0.0035 | 100 |
| C2, C5, C6, C8, C9, C10, C11, C12, C13, C14, C15, C16 | 12 | Capacitor 100nF 50V X7R 0805 (JLCPCB basic part; price: JLCPCB's parts list) | YAGEO CC0805KRX7R9BB104 | LCSC C49678 | USD 0.0205 | 20 |
| U2 | 1 | Ideal diode 1.5 A, SC-70-6 (0.65 mm pitch) | TI LM66100DCKR | LCSC C2869734 | USD 0.2089 | 5 |
| R70, R71, R51, R60, R64, R65 | 6 | Resistor 10k 1% 0805 (pull-ups: the ladder, the encoder, I2C, the opto output) | UNI-ROYAL 0805W8F1002T5E | LCSC C17414 | USD 0.0034 | 100 |
| R61 | 1 | Resistor 2.2k 1% 0805 (ladder: OK) | UNI-ROYAL 0805W8F2201T5E | LCSC C17520 | USD 0.0050 | 100 |
| R62 | 1 | Resistor 6.8k 1% 0805 (ladder: BACK) | UNI-ROYAL 0805W8F6801T5E | LCSC C17772 | USD 0.0028 | 100 |
| R63 | 1 | Resistor 22k 1% 0805 (ladder: the encoder's push) | UNI-ROYAL 0805W8F2202T5E | LCSC C17560 | USD 0.0048 | 100 |
| SW7 | 1 | Rotary encoder EC11, vertical, 18 detents / 9 pulses, push switch, 20 mm flat (D) shaft, through hole, top side | ALPS EC11E09244BS | LCSC C470742 | USD 2.3275 | 1 |
| C4 | 1 (not fitted) | Electrolytic 100uF 16V 5 x 5.4 mm (not fitted by default) | ROQANG RVT1C101M0505 | LCSC C2977550 | USD 0.0356 | 20 |
| SW1, SW6 | 2 | Tactile switch 6 x 6 mm, through hole, 9.0 mm tall, top side (OK, BACK), soldered by the user (JLC refused the whole HRO K2-1102DP family for assembly on 2026-11-09); 9.0 mm: the lid's button caps 0.5 mm longer than for 9.5 | HRO K2-1102DP-K4SW-04 | LCSC C111992 | USD 0.0653 | 1 |
| U5 | 1 | I2C GPIO expander, 8 bit, quasi-bidirectional, SOIC-16 wide (the modular variant: CLOCK / RESET; price: JLCPCB's parts list) | NXP PCF8574T/3 | LCSC C7605 | USD 2.0313 | 1 |
| D3, D4, D5, D6 | 4 | Diode pair in series BAV99, SOT-23, same pinout as the BAT54S (1 = A1, 2 = K2, 3 = K1/A2): the modular outputs' clamp to GND and +5V; v5c 2026-11-09: a JLC basic part instead of the extended BAT54S (silicon, clamps at ~0.7 V instead of ~0.35 V past the rails: fine behind the 1 k) | BAV99 | LCSC C2500 | USD 0.0000 | 20 |
| U3, U6, U7, U8, U9 | 5 | Buffer 74AHCT1G125, SOT-23-5 (4.5 to 5.5 V) | TI SN74AHCT1G125DBVR | LCSC C7484 | USD 0.1009 | 5 |
| J2, J3, J4, J5 | 4 | 3.5 mm stereo jack, right angle, SURFACE MOUNT (4 tabs 1.5 x 2.5, 2 pegs 1.3), plug from the front, top side: the four MIDI outputs' jacks (J2..J5 are BOM lines; the pads are in J6..J9's footprint). Surface-mount so nothing of it goes through the board under the neighbouring DIN bodies | XKB PJ-320D-B-SMT | LCSC C2884940 | USD 0.0000 | 5 |
| SW2 | 1 | Slide switch DPDT, surface mount, 6 tabs 2.5 mm, 7.7 x 3.55 mm, knob 3.0 mm (OUT1's TRS type A / B: it sits over the DIN's body, where a through-hole switch's pins would hit it) | XKB SS-3235S-L2 | LCSC C500056 | USD 0.0000 | 5 |
| SW3, SW4, SW5 | 3 | Slide switch DPDT, 6 pins 2.5 mm, 9.1 x 3.5 mm, handle 1.5 mm (TRS type A / B), face side; OUT2..4 | SHOU HAN MSS22D18G2 | LCSC C431542 | USD 0.0996 | 5 |
| U4 | 1 | Optocoupler H11L1, Schmitt trigger, open collector, DIP-6 (MIDI IN on OUT1) | EVERLIGHT H11L1 | LCSC C78588 | USD 0.3507 | 5 |
| D2 | 1 | Diode 1N4148W, SOD-123 (the opto LED's reverse protection) | Semtech 1N4148W | LCSC C81598 | USD 0.0125 | 50 |
| R50 | 1 | Resistor 220 1% 0805 (MIDI IN, CA-033 / MIDI 1.0) | UNI-ROYAL 0805W8F2200T5E | LCSC C17557 | USD 0.0030 | 100 |
| R8, R11, R21, R12, R22, R13, R23, R14, R24 | 9 (not fitted) | Axial pads, not fitted (a bench fix: an axial resistor in place of the 1206s, with them removed) | - | - - | USD 0.0000 | 0 |
| R31 | 1 | Resistor 47 ohm 1% 0.25 W 1206 (OUT1's RC: OUT1 doubles as MIDI IN) | UNI-ROYAL 1206W4F470JT5E | LCSC C17969 | USD 0.0053 | 1 |
| R32, R33, R34 | 3 | Resistor 10 ohm 1% 0.25 W 1206 (RC, data) | UNI-ROYAL 1206W4F100JT5E | LCSC C17903 | USD 0.0027 | 100 |
| R41, R81, R42, R82, R43, R83, R44, R84 | 8 | Resistor 100 ohm 1% 0.25 W 1206, two in parallel = the 50 ohm source RA (0.5 W together; v5c 2026-11-09: 100 ohm is a JLC basic part, 68 is not; the loop current ~5.9 mA instead of ~6.8 mA) | UNI-ROYAL 1206W4F1000T5E | LCSC C17901 | USD 0.0000 | 100 |
| R9 | 1 | Resistor 300 ohm 1% 0.25 W 1206 (the LED's data; 300 is a JLC basic part, 330 is not) | UNI-ROYAL 1206W4F3000T5E | LCSC C17887 | USD 0.0000 | 100 |
| LED1 | 1 | RGB LED, addressable, 3.7 x 3.5 x 1.95 mm, top emitting (the beat LED) | OPSCO SK6812MINI-HS | LCSC C2922787 | USD 0.1085 | 5 |
| J10 | 1 | OLED module 0.96 in 128 x 64, white, SSD1315 (SSD1306 commands), I2C, 27.3 x 27.8 mm, 4 holes 2.54 mm (GND VCC SCL SDA) | HS HS96L03W2C03 | LCSC C5248080 | USD 0.0000 | 1 |
| (J10) | 1 | Pin header 1x4, 2.54 mm (the OLED module's legs) | XFCN PZ254V-11-04P | LCSC C2691448 | USD 0.0276 | 20 |
| J11, J12, J13, J14 | 4 | 3.5 mm stereo jack, right angle, plug from the front, 4 pins (its switch pin left open), top side | XKB PJ-320A | LCSC C2884926 | USD 0.1458 | 5 |
| J6, J7, J8, J9 | 4 | DIN-5 180 degree, PCB right angle, 7 pins, no locating pegs, bottom side | HOOYA DIN-504B-M10 | LCSC C2939346 | USD 0.3764 | 5 |

Test points TP1 to TP4 and the bypass jumpers JP8, JP11 to JP24 are bare pads, not parts.

## Total, one board

| Build | Parts at unit price | With each shop's minimum order |
|---|---|---|
| 4 jacks + 4 DINs + 4 A/B switches, OLED, 1 LED + the modular outputs | USD 16.52 | USD 26.86 |

USD: LCSC and Seeed (the XIAO). The bare board is ordered at JLCPCB with another board and is not in these totals.

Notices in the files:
hardware/pcb/README.md:
last commit to the file b0035c5 (2026-06-23), licence CC BY-SA 4.0. It has both a through-hole pad (0.889 mm drill)
